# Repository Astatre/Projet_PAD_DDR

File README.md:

# Projet_PAD_DDR

## Description

Le projet **Projet_PAD_DDR** vise à développer un pad de jeu personnalisé, intégrant à la fois les composants matériels (hardware) et logiciels (software) nécessaires à sa réalisation. Ce pad est conçu pour être utilisé dans des jeux de rythme ou d'autres applications interactives, offrant une expérience de jeu immersive et personnalisable.

## Objectifs

- Concevoir et assembler le hardware du pad, incluant des boutons et interfaces de connexion.
- Développer le software pour gérer les entrées utilisateur, traiter les signaux et communiquer avec des appareils externes (comme un ordinateur ou une console de jeu).

## Cahier des Charges

### Fonctionnalités Requises
- **Hardware** :
    - Boutons résistants et sensibles pour une détection précise des pressions.
    - Interface de connexion USB pour une intégration facile.
    - Alimentation via câble.
- **Software** :
    - Gestion des entrées en temps réel.
    - Compatibilité avec des systèmes d'exploitation courants (Windows, Linux).

### Contraintes
- Facilité d'assemblage et de maintenance.
- Respect de l'environnement.

## Structure du Projet

- **Hardware** : Schémas et composants.
- **Software** : Code source, bibliothèques et exemples d'utilisation.
- **Modèles 3D** : Ensemble des modèles d'interrupteurs pour permettre un ajustement personnalisé.

## Installation et Utilisation

1. **Matériel** : Créer le PCB présent dans le dossier `Kicad`. (V2 : connexion USB Micro, V3 : connexion USB-C)
2. **PAD** : Suivre les différents schémas et utiliser les différents modèles pour les interrupteurs dans le dossier `Model`.
3. **Logiciel** : Cloner le dépôt et compiler le code selon les instructions dans le dossier `Cube Workspace`.
4. **Test** : Connecter le pad à votre appareil et tester les fonctionnalités.

## Contribution

Les contributions sont les bienvenues ! Veuillez soumettre des issues ou des pull requests pour améliorer le projet.

## Licence

Ce projet est sous licence [MIT](https://opensource.org/licenses/MIT).

## Auteurs

- [Drault, Sourbé, Sayavong, Dalmon] - Développeurs principaux

Pour plus d'informations, consultez les fichiers dans le dépôt.

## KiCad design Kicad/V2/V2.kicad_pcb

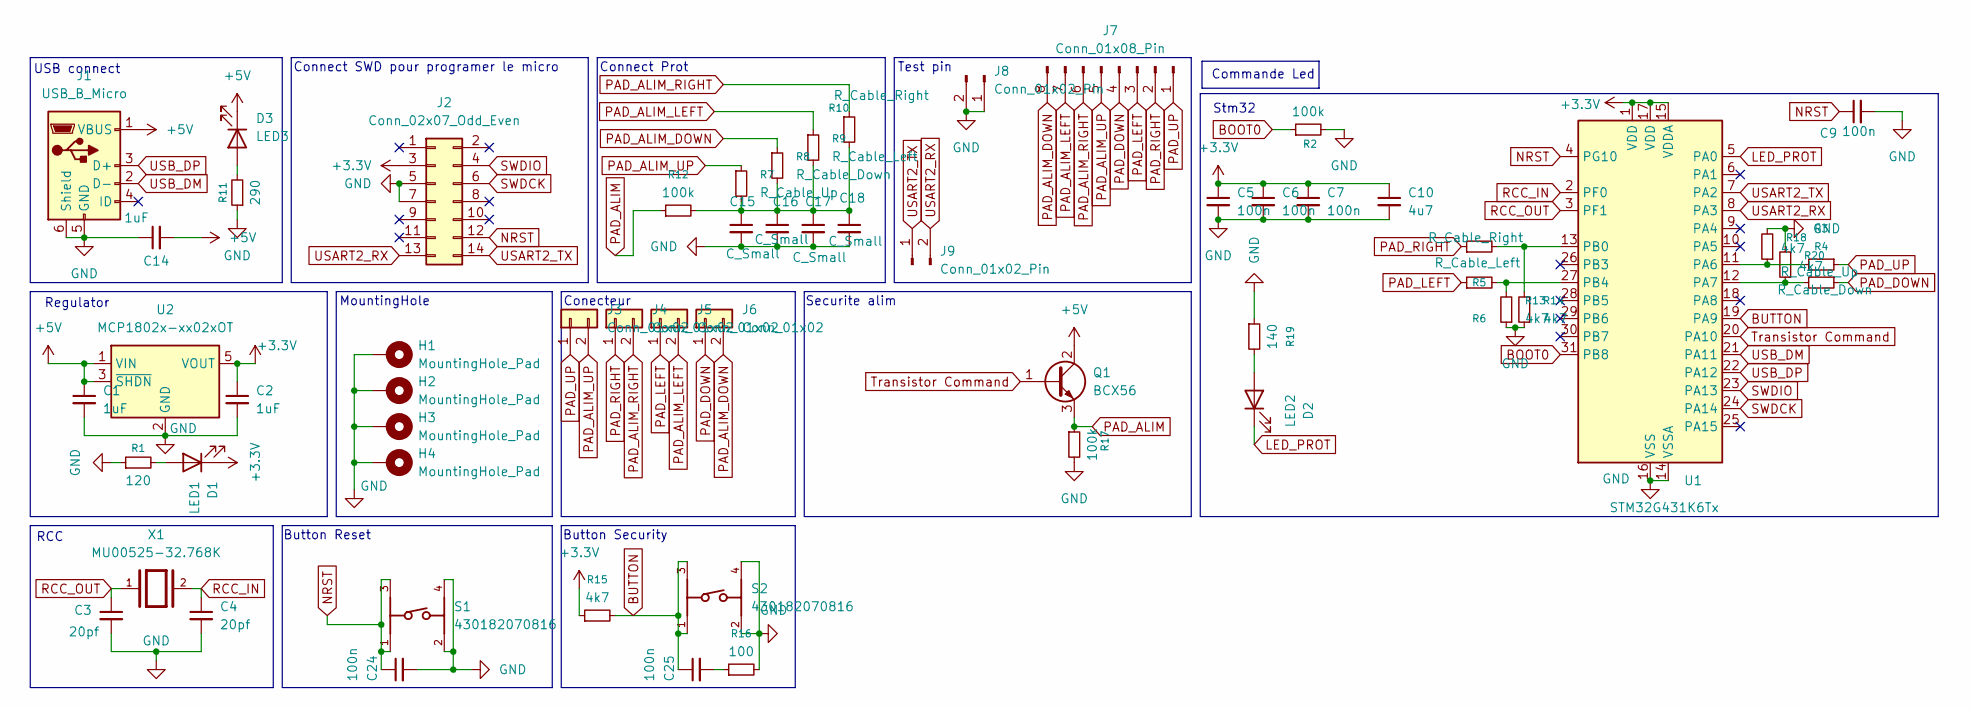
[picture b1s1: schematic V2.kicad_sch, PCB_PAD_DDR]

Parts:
C1, C2, C14: 1uF; C_0805_2012Metric_Pad1.18x1.45mm_HandSolder
C3, C4: 20pf; C_0805_2012Metric_Pad1.18x1.45mm_HandSolder
C5, C6, C7, C9, C24, C25: 100n; C_0805_2012Metric_Pad1.18x1.45mm_HandSolder
C10: 4u7; C_0805_2012Metric_Pad1.18x1.45mm_HandSolder
C15, C16, C17, C18: C_Small; C_0805_2012Metric_Pad1.18x1.45mm_HandSolder
D1: LED1; LED_0805_2012Metric_Pad1.15x1.40mm_HandSolder
D2: LED2; LED_0805_2012Metric_Pad1.15x1.40mm_HandSolder
D3: LED3; LED_0805_2012Metric_Pad1.15x1.40mm_HandSolder
H1, H2, H3, H4: MountingHole_Pad; MountingHole_3.2mm_M3_DIN965_Pad
J1: USB_B_Micro; USB_Micro-B_Wuerth_629105150521
J2: Conn_02x07_Odd_Even; PinHeader_2x07_P1.27mm_Vertical_SMD
J3, J4, J5, J6: Conn_01x02; JST_XH_B2B-XH-A_1x02_P2.50mm_Vertical
J7: Conn_01x08_Pin; PinHeader_1x08_P2.54mm_Vertical
J8, J9: Conn_01x02_Pin; PinHeader_1x02_P2.54mm_Vertical
Q1: BCX56; SOT-223
R1: 120; R_0805_2012Metric_Pad1.20x1.40mm_HandSolder
R2, R12, R17: 100k; R_0805_2012Metric_Pad1.20x1.40mm_HandSolder
R3, R7: R_Cable_Up; R_0805_2012Metric_Pad1.20x1.40mm_HandSolder
R4, R8: R_Cable_Down; R_0805_2012Metric_Pad1.20x1.40mm_HandSolder
R5, R10: R_Cable_Right; R_0805_2012Metric_Pad1.20x1.40mm_HandSolder
R6, R9: R_Cable_Left; R_0805_2012Metric_Pad1.20x1.40mm_HandSolder
R11: 290; R_0805_2012Metric_Pad1.20x1.40mm_HandSolder
R13, R14, R15, R18, R20: 4k7; R_0805_2012Metric_Pad1.20x1.40mm_HandSolder
R16: 100; R_0805_2012Metric_Pad1.20x1.40mm_HandSolder
R19: 140; R_0805_2012Metric_Pad1.20x1.40mm_HandSolder
S1, S2: 430182070816
U1: STM32G431K6Tx; LQFP-32_7x7mm_P0.8mm
U2: MCP1802x-xx02xOT; SOT-23-5
X1: MU00525-32.768K; XTAL_MU00525-32.768K

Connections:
Transistor Command: Q1.1 (B), U1.20 (PA10)
+3.3V: C2.1, C5.1, C6.1, C7.1, C10.1, D1.1 (K), J2.3, R15.1, U1.1 (VDD), U1.15 (VDDA), U1.17 (VDD), U2.5 (VOUT)
+5V: C1.1, C14.2, D3.1 (K), J1.1 (VBUS), Q1.2 (C), U2.1 (VIN), U2.3 (~SHDN)
BOOT0: R2.1, U1.31 (PB8)
BUTTON: C25.1, R15.2, S2.1, S2.3, U1.19 (PA9)
GND: C1.2, C2.2, C3.2, C4.2, C5.2, C6.2, C7.2, C9.2, C10.2, C14.1, C15.2, C16.2, C17.2, C18.2, C24.2, H1.1, H2.1, H3.1, H4.1, J1.5 (GND), J1.6 (Shield), J2.5, J2.7, J8.1, J8.2, R1.1, R2.2, R11.1, R13.1, R14.1, R16.2, R17.2, R18.2, R19.1, R20.2, S1.2, S1.4, S2.2, S2.4, U1.14 (VSSA), U1.16 (VSS), U1.32 (VSS), U2.2 (GND)
LED_PROT: D2.1 (K), U1.5 (PA0)
NRST: C9.1, C24.1, J2.12, S1.1, S1.3, U1.4 (PG10)
unnamed: C15.1, C16.1, C17.1, C18.1, R7.2, R8.2, R9.2, R10.2, R12.2
unnamed: C25.2, R16.1
unnamed: D1.2 (A), R1.2
unnamed: D2.2 (A), R19.2
unnamed: D3.2 (A), R11.2
unnamed: R3.2, R18.1, U1.11 (PA6)
unnamed: R4.2, R20.1, U1.12 (PA7)
unnamed: R5.2, R14.2, U1.13 (PB0)
unnamed: R6.2, R13.2, U1.27 (PB4)
PAD_ALIM: Q1.3 (E), R12.1, R17.1
PAD_ALIM_DOWN: J6.2, J7.8, R8.1
PAD_ALIM_LEFT: J5.2, J7.7, R9.1
PAD_ALIM_RIGHT: J4.2, J7.6, R10.1
PAD_ALIM_UP: J3.2, J7.5, R7.1
PAD_DOWN: J6.1, J7.4, R4.1
PAD_LEFT: J5.1, J7.3, R6.1
PAD_RIGHT: J4.1, J7.2, R5.1
PAD_UP: J3.1, J7.1, R3.1
RCC_IN: C4.1, U1.2 (PF0), X1.2
RCC_OUT: C3.1, U1.3 (PF1), X1.1
SWDCK: J2.6, U1.24 (PA14)
SWDIO: J2.4, U1.23 (PA13)
USART2_RX: J2.13, J9.2, U1.8 (PA3)
USART2_TX: J2.14, J9.1, U1.7 (PA2)
USB_DM: J1.2 (D-), U1.21 (PA11)
USB_DP: J1.3 (D+), U1.22 (PA12)

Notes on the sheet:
Securite alim
Regulator
Commande Led
MountingHole
Stm32
Test pin
USB connect
Connect SWD pour programer le micro
Button Security
Button Reset
RCC
Conecteur
Connect Prot

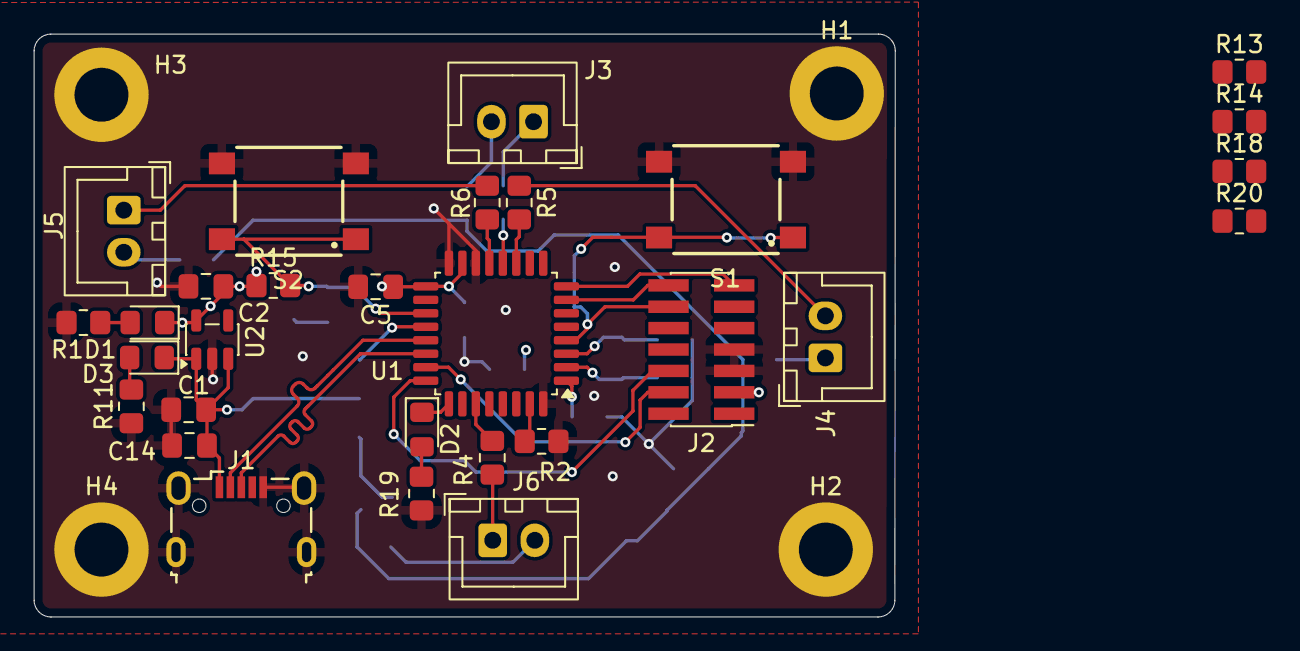
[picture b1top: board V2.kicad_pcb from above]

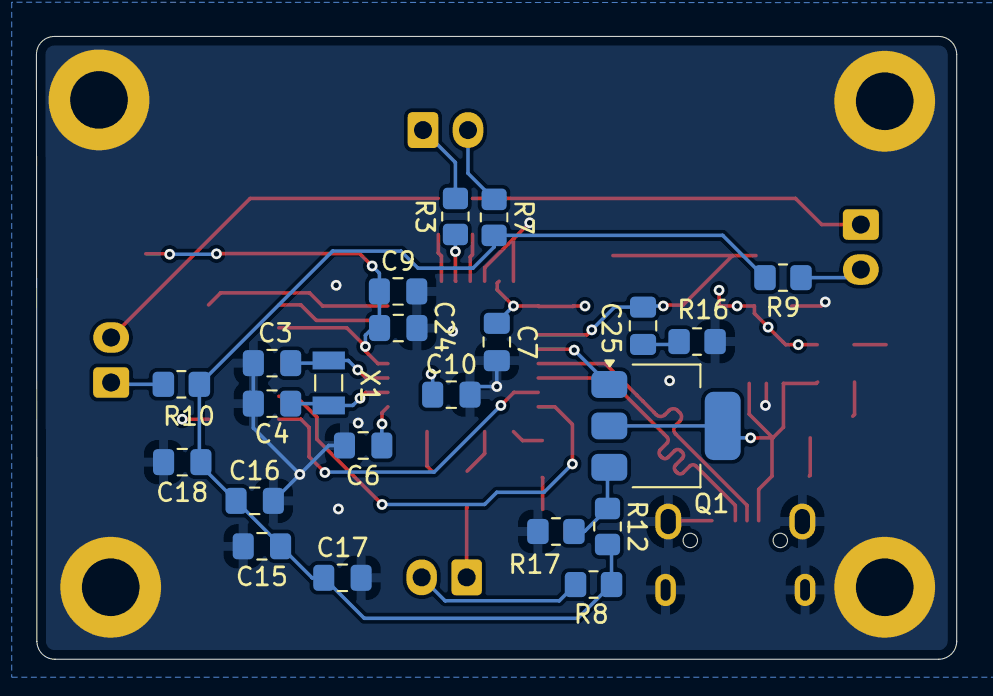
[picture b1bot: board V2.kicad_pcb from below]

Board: 4 copper layers, 51.1 x 34.6 mm, 55 parts (22 on the bottom side), 34 nets.

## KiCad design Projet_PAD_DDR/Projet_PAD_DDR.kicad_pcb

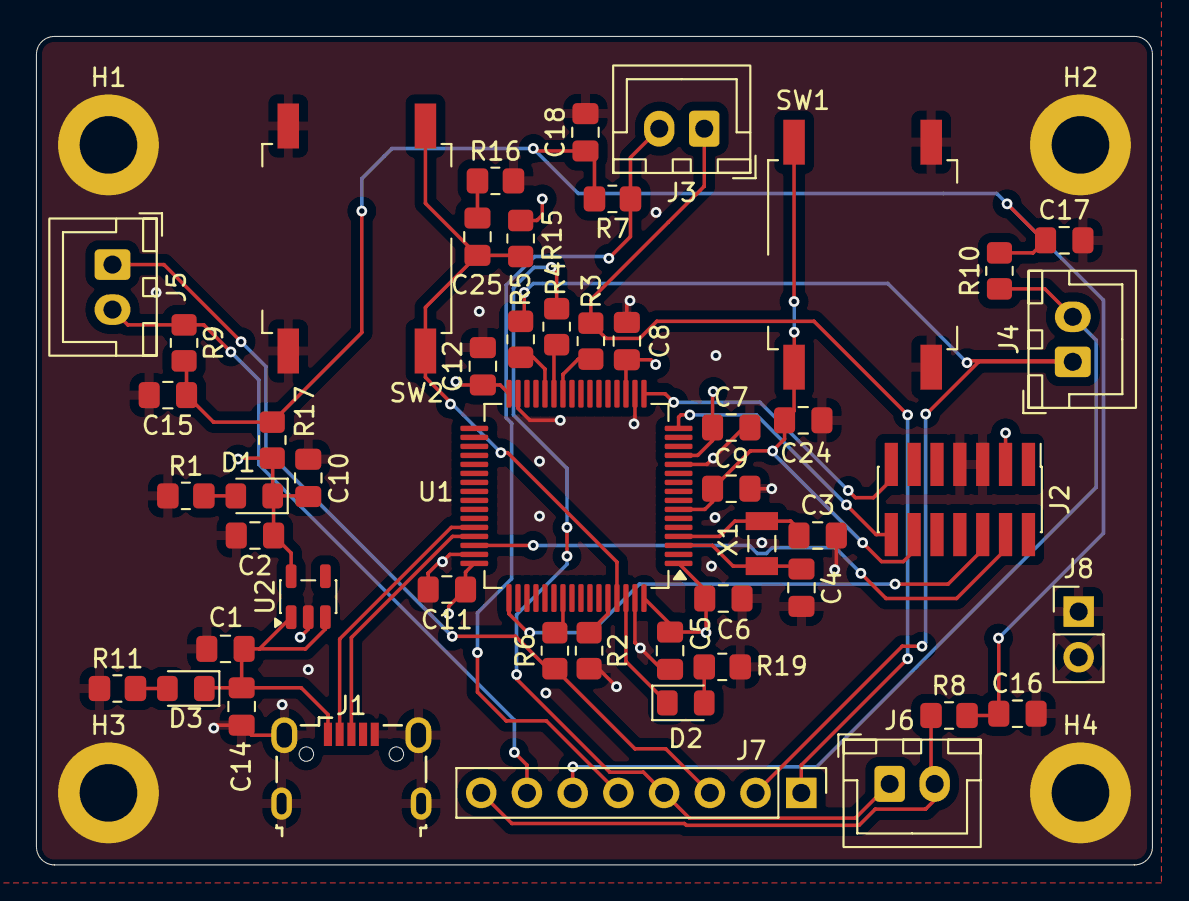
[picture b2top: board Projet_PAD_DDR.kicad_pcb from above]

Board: 4 copper layers, 62.0 x 46.0 mm, 54 parts (0 on the bottom side), 32 nets.

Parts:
C1, C2, C14: 1uF; C_0805_2012Metric_Pad1.18x1.45mm_HandSolder
C3, C4: 20pf; C_0805_2012Metric_Pad1.18x1.45mm_HandSolder
C5, C6, C7, C8, C9, C11, C12, C24, C25: 100n; C_0805_2012Metric_Pad1.18x1.45mm_HandSolder
C10: 4u7; C_0805_2012Metric_Pad1.18x1.45mm_HandSolder
C15, C16, C17, C18: C_Small; C_0805_2012Metric_Pad1.18x1.45mm_HandSolder
D1: LED1; LED_0805_2012Metric_Pad1.15x1.40mm_HandSolder
D2: LED2; LED_0805_2012Metric_Pad1.15x1.40mm_HandSolder
D3: LED3; LED_0805_2012Metric_Pad1.15x1.40mm_HandSolder
H1, H2, H3, H4: MountingHole_Pad; MountingHole_3.2mm_M3_DIN965_Pad
J1: USB_B_Micro; USB_Micro-B_Wuerth_629105150521
J2: Conn_02x07_Odd_Even; PinHeader_2x07_P1.27mm_Vertical_SMD
J3, J4, J5, J6: Conn_01x02; JST_XH_B2B-XH-A_1x02_P2.50mm_Vertical
J7: Conn_01x08_Pin; PinHeader_1x08_P2.54mm_Vertical
J8: Conn_01x02_Pin; PinHeader_1x02_P2.54mm_Vertical
R1: 120; R_0805_2012Metric_Pad1.20x1.40mm_HandSolder
R2, R17: 100k; R_0805_2012Metric_Pad1.20x1.40mm_HandSolder
R3, R7: R_Cable_Up; R_0805_2012Metric_Pad1.20x1.40mm_HandSolder
R4, R8: R_Cable_Down; R_0805_2012Metric_Pad1.20x1.40mm_HandSolder
R5, R10: R_Cable_Right; R_0805_2012Metric_Pad1.20x1.40mm_HandSolder
R6, R9: R_Cable_Left; R_0805_2012Metric_Pad1.20x1.40mm_HandSolder
R11: 290; R_0805_2012Metric_Pad1.20x1.40mm_HandSolder
R15: 4k7; R_0805_2012Metric_Pad1.20x1.40mm_HandSolder
R16: 100; R_0805_2012Metric_Pad1.20x1.40mm_HandSolder
R19: 140; R_0805_2012Metric_Pad1.20x1.40mm_HandSolder
SW1, SW2: SW_MEC_5E; SW_MEC_5GSH9
U1: STM32L476RGTx; LQFP-64_10x10mm_P0.5mm
U2: MCP1802x-xx02xOT; SOT-23-5
X1: MU00525-32.768K; XTAL_MU00525-32.768K

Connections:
+3.3V: C2.1, C5.1, C6.1, C7.1, C8.1, C10.1, C11.1, C12.1, D1.1 (K), J2.3, R15.1, R17.1, U1.1 (VBAT), U1.13 (VDDA), U1.19 (VDD), U1.32 (VDD), U1.48 (VDDUSB), U1.64 (VDD), U2.5 (VOUT)
+5V: C1.1, C14.2, D3.1 (K), J1.1 (VBUS), U2.1 (VIN), U2.3 (~SHDN)
BOOT0: R2.1, U1.60 (BOOT0)
BUTTON: C25.1, R15.2, SW2.1, SW2.2, U1.61 (PB8)
GND: C1.2, C2.2, C3.2, C4.2, C5.2, C6.2, C7.2, C8.2, C9.2, C10.2, C11.2, C12.2, C14.1, C15.2, C16.2, C17.2, C18.2, C24.2, H1.1, H2.1, H3.1, H4.1, J1.5 (GND), J1.6 (Shield), J2.5, J2.7, J8.1, J8.2, R1.1, R2.2, R11.1, R16.2, R19.1, SW1.3 (K), SW1.4 (A), SW2.3 (K), SW2.4 (A), U1.12 (VSSA), U1.18 (VSS), U1.31 (VSS), U1.47 (VSS), U1.63 (VSS), U2.2 (GND)
LED_PROT: D2.1 (K), U1.62 (PB9)
NRST: C9.1, C24.1, J2.12, SW1.1, SW1.2, U1.7 (NRST)
unnamed: C25.2, R16.1
unnamed: D1.2 (A), R1.2
unnamed: D2.2 (A), R19.2
unnamed: D3.2 (A), R11.2
unnamed: R3.2, U1.26 (PB0)
unnamed: R4.2, U1.27 (PB1)
unnamed: R5.2, U1.28 (PB2)
unnamed: R6.2, U1.55 (PB3)
PAD_ALIM: C15.1, C16.1, C17.1, C18.1, R7.2, R8.2, R9.2, R10.2, R17.2
PAD_ALIM_DOWN: J6.2, J7.8, R8.1
PAD_ALIM_LEFT: J5.2, J7.7, R9.1
PAD_ALIM_RIGHT: J4.2, J7.6, R10.1
PAD_ALIM_UP: J3.2, J7.5, R7.1
PAD_DOWN: J6.1, J7.4, R4.1
PAD_LEFT: J5.1, J7.3, R6.1
PAD_RIGHT: J4.1, J7.2, R5.1
PAD_UP: J3.1, J7.1, R3.1
RCC_IN: C4.1, U1.3 (PC14), X1.2
RCC_OUT: C3.1, U1.4 (PC15), X1.1
SWDCK: J2.6, U1.49 (PA14)
SWDIO: J2.4, U1.46 (PA13)
USART2_RX: J2.13, U1.17 (PA3)
USART2_TX: J2.14, U1.16 (PA2)
USB_DM: J1.2 (D-), U1.44 (PA11)
USB_DP: J1.3 (D+), U1.45 (PA12)

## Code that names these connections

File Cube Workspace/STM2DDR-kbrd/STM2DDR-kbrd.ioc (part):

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Mcu.Name=STM32G431K(6-8-B)Tx
Mcu.Package=LQFP32
Mcu.UserName=STM32G431K6Tx
PA0.GPIOParameters=GPIO_Label
PA0.GPIO_Label=LED_PROT(Output)
PA0.Signal=GPIO_Output
PA10.GPIOParameters=GPIO_Label
PA10.GPIO_Label=Transistor_Command(Output)
PA10.Signal=GPIO_Output
PA11.Mode=Device
PA11.Signal=USB_DM
PA12.Mode=Device
PA12.Signal=USB_DP
PA13.Mode=Serial_Wire
PA13.Signal=SYS_JTMS-SWDIO
PA14.Mode=Serial_Wire
PA14.Signal=SYS_JTCK-SWCLK
PA2.Mode=Asynchronous
PA2.Signal=USART2_TX
PA3.Mode=Asynchronous
PA3.Signal=USART2_RX
PA6.GPIOParameters=GPIO_PuPd,GPIO_Label,GPIO_ModeDefaultEXTI
PA6.GPIO_Label=PAD_UP(EXTI)
PA6.GPIO_ModeDefaultEXTI=GPIO_MODE_IT_RISING_FALLING
PA6.GPIO_PuPd=GPIO_NOPULL
PA6.Signal=GPXTI6
PA7.GPIOParameters=GPIO_PuPd,GPIO_Label,GPIO_ModeDefaultEXTI
PA7.GPIO_Label=PAD_DOWN(EXTI)
PA7.GPIO_ModeDefaultEXTI=GPIO_MODE_IT_RISING_FALLING
PA7.GPIO_PuPd=GPIO_NOPULL
PA7.Signal=GPXTI7
PA9.GPIOParameters=GPIO_Label,GPIO_ModeDefaultEXTI
PA9.GPIO_Label=BUTTON(EXTI)
PA9.GPIO_ModeDefaultEXTI=GPIO_MODE_IT_FALLING
PA9.Signal=GPXTI9
PB0.GPIOParameters=GPIO_PuPd,GPIO_Label,GPIO_ModeDefaultEXTI
PB0.GPIO_Label=PAD_RIGHT(EXTI)
PB0.GPIO_ModeDefaultEXTI=GPIO_MODE_IT_RISING_FALLING
PB0.GPIO_PuPd=GPIO_NOPULL
PB0.Signal=GPXTI0
PB4.GPIOParameters=GPIO_PuPd,GPIO_Label,GPIO_ModeDefaultEXTI
PB4.GPIO_Label=PAD_LEFT(EXTI)
PB4.GPIO_ModeDefaultEXTI=GPIO_MODE_IT_RISING_FALLING
PB4.GPIO_PuPd=GPIO_NOPULL
PB4.Signal=GPXTI4
PF0-OSC_IN.Mode=HSE-External-Oscillator
PF0-OSC_IN.Signal=RCC_OSC_IN
PF1-OSC_OUT.Mode=HSE-External-Oscillator
PF1-OSC_OUT.Signal=RCC_OSC_OUT
RCC.HSE_VALUE=8000000
RCC.SYSCLKFreq_VALUE=16000000
board=custom

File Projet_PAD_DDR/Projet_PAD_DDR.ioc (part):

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Mcu.Name=STM32L476R(C-E-G)Tx
Mcu.Package=LQFP64
Mcu.UserName=STM32L476RGTx
PA11.Mode=Host_Only
PA11.Signal=USB_OTG_FS_DM
PA12.Mode=Host_Only
PA12.Signal=USB_OTG_FS_DP
PA2.Mode=Asynchronous
PA2.Signal=USART2_TX
PA3.Mode=Asynchronous
PA3.Signal=USART2_RX
PB0.GPIOParameters=GPIO_Label
PB0.GPIO_Label=UP
PB0.Signal=GPXTI0
PB1.GPIOParameters=GPIO_Label
PB1.GPIO_Label=DOWN
PB1.Signal=GPXTI1
PB2.GPIOParameters=GPIO_Label
PB2.GPIO_Label=RIGHT
PB2.Signal=GPXTI2
PB3\ (JTDO-TRACESWO).GPIOParameters=GPIO_Label
PB3\ (JTDO-TRACESWO).GPIO_Label=LEFT
PB3\ (JTDO-TRACESWO).Signal=GPXTI3
PB8.GPIOParameters=GPIO_Label
PB8.GPIO_Label=BOUTTON
PB8.Signal=GPXTI8
PB9.GPIOParameters=GPIO_Label
PB9.GPIO_Label=LED
PB9.Signal=GPIO_Output
PC14-OSC32_IN\ (PC14).Mode=LSE-External-Oscillator
PC14-OSC32_IN\ (PC14).Signal=RCC_OSC32_IN
PC15-OSC32_OUT\ (PC15).Mode=LSE-External-Oscillator
PC15-OSC32_OUT\ (PC15).Signal=RCC_OSC32_OUT
RCC.HSE_VALUE=8000000
board=custom

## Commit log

2026-02-08 First Schematic
    Besoin de dimensionné les composant et de choisir les led.
2026-02-12 Version test première verification
2026-02-12 Version a verifier
2026-02-16 La v2 avec un autre Mc
2026-02-19 Kicad a verif
2026-02-19 Changement detaille de piste
2026-02-21 Ajout des projets Cube pour la Nucleo
2026-02-21 Revert "Ajout des projets Cube pour la Nucleo"
    This reverts commit 23604323aca1d2e4fba32a353018f6e3ff98db90.
2026-02-21 Correction de l'ajout des projets Cube pour la Nucleo
2026-02-21 Ajout du projet Cube pour le microprocesseur final
2026-03-18 Added springs stl
2026-03-18 Réorganisation des fichiers
2026-03-18 Réorganisation des fichiers et ajout du fichier CAD
2026-03-19 Ajout v3
2026-03-26 Version final
2026-03-26 Dernière version qui marche bien :)
2026-03-26 Version final + seri
2026-04-09 Version merge
2026-04-13 Ajout des autres pièces
2026-04-13 Suppression des anciens fichiers
2026-04-16 Revert "Merge branch 'Modèles-3D'"
    This reverts commit f74af3508975ee8b5dad27d226e8cc0d71e5569e, reversing
    changes made to eb41a01a9987be4433b5e7c587b1462da7b78b96.
